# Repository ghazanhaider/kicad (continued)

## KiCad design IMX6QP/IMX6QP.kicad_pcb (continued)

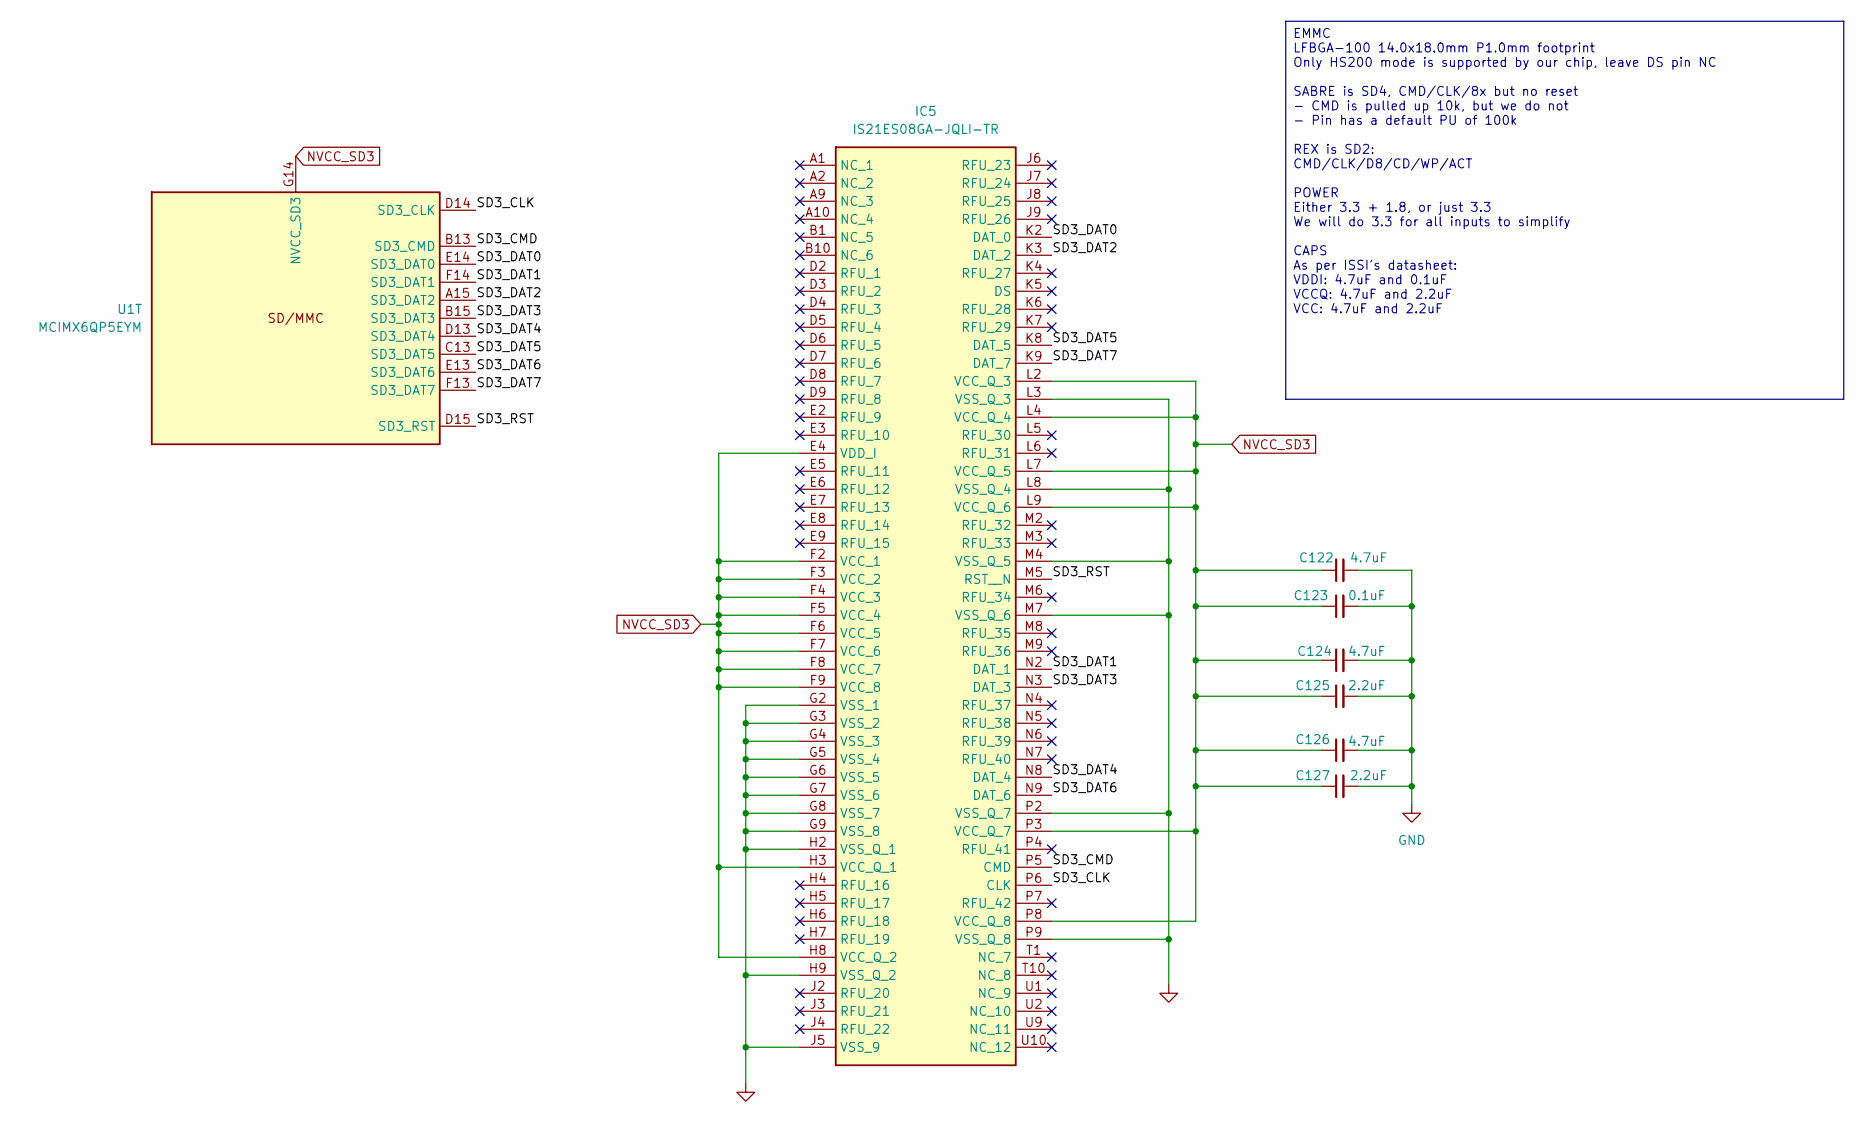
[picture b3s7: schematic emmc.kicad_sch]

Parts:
C122, C124, C126: 4.7uF; C_0603_1608Metric
C123: 0.1uF; C_0402_1005Metric
C125, C127: 2.2uF; C_0603_1608Metric
IC5: IS21ES08GA-JQLI-TR; BGA100C100P10X17_1400X1800X140; Mouser Part Number 870-IS21ES08GAJQLIT
U1: MCIMX6QP5EYM; BGA-624_21x21mm_Layout25x25_P0.8mm

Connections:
3V3_SW2: C122.1, C123.1, C124.1, C125.1, C126.1, C127.1, IC5.E4 (VDD_I), IC5.F2 (VCC_1), IC5.F3 (VCC_2), IC5.F4 (VCC_3), IC5.F5 (VCC_4), IC5.F6 (VCC_5), IC5.F7 (VCC_6), IC5.F8 (VCC_7), IC5.F9 (VCC_8), IC5.H3 (VCC_Q_1), IC5.H8 (VCC_Q_2), IC5.L2 (VCC_Q_3), IC5.L4 (VCC_Q_4), IC5.L7 (VCC_Q_5), IC5.L9 (VCC_Q_6), IC5.P3 (VCC_Q_7), IC5.P8 (VCC_Q_8), U1.G14 (NVCC_SD3); also elsewhere on the board
/eMMC/SD3_CLK: IC5.P6 (CLK), U1.D14 (SD3_CLK)
/eMMC/SD3_CMD: IC5.P5 (CMD), U1.B13 (SD3_CMD)
/eMMC/SD3_DAT0: IC5.K2 (DAT_0), U1.E14 (SD3_DAT0)
/eMMC/SD3_DAT1: IC5.N2 (DAT_1), U1.F14 (SD3_DAT1)
/eMMC/SD3_DAT2: IC5.K3 (DAT_2), U1.A15 (SD3_DAT2)
/eMMC/SD3_DAT3: IC5.N3 (DAT_3), U1.B15 (SD3_DAT3)
/eMMC/SD3_DAT4: IC5.N8 (DAT_4), U1.D13 (SD3_DAT4)
/eMMC/SD3_DAT5: IC5.K8 (DAT_5), U1.C13 (SD3_DAT5)
/eMMC/SD3_DAT6: IC5.N9 (DAT_6), U1.E13 (SD3_DAT6)
/eMMC/SD3_DAT7: IC5.K9 (DAT_7), U1.F13 (SD3_DAT7)
/eMMC/SD3_RST: IC5.M5 (RST__N), U1.D15 (SD3_RST)
GND: C122.2, C123.2, C124.2, C125.2, C126.2, C127.2, IC5.G2 (VSS_1), IC5.G3 (VSS_2), IC5.G4 (VSS_3), IC5.G5 (VSS_4), IC5.G6 (VSS_5), IC5.G7 (VSS_6), IC5.G8 (VSS_7), IC5.G9 (VSS_8), IC5.H2 (VSS_Q_1), IC5.H9 (VSS_Q_2), IC5.J5 (VSS_9), IC5.L3 (VSS_Q_3), IC5.L8 (VSS_Q_4), IC5.M4 (VSS_Q_5), IC5.M7 (VSS_Q_6), IC5.P2 (VSS_Q_7), IC5.P9 (VSS_Q_8); also elsewhere on the board

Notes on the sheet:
EMMC LFBGA-100 14.0x18.0mm P1.0mm footprint Only HS200 mode is supported by our chip, leave DS pin NC SABRE is SD4, CMD/CLK/8x but no reset - CMD is pulled up 10k, but we do not - Pin has a default PU of 100k REX is SD2: CMD/CLK/D8/CD/WP/ACT POWER Either 3.3 + 1.8, or just 3.3 We will do 3.3 for al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

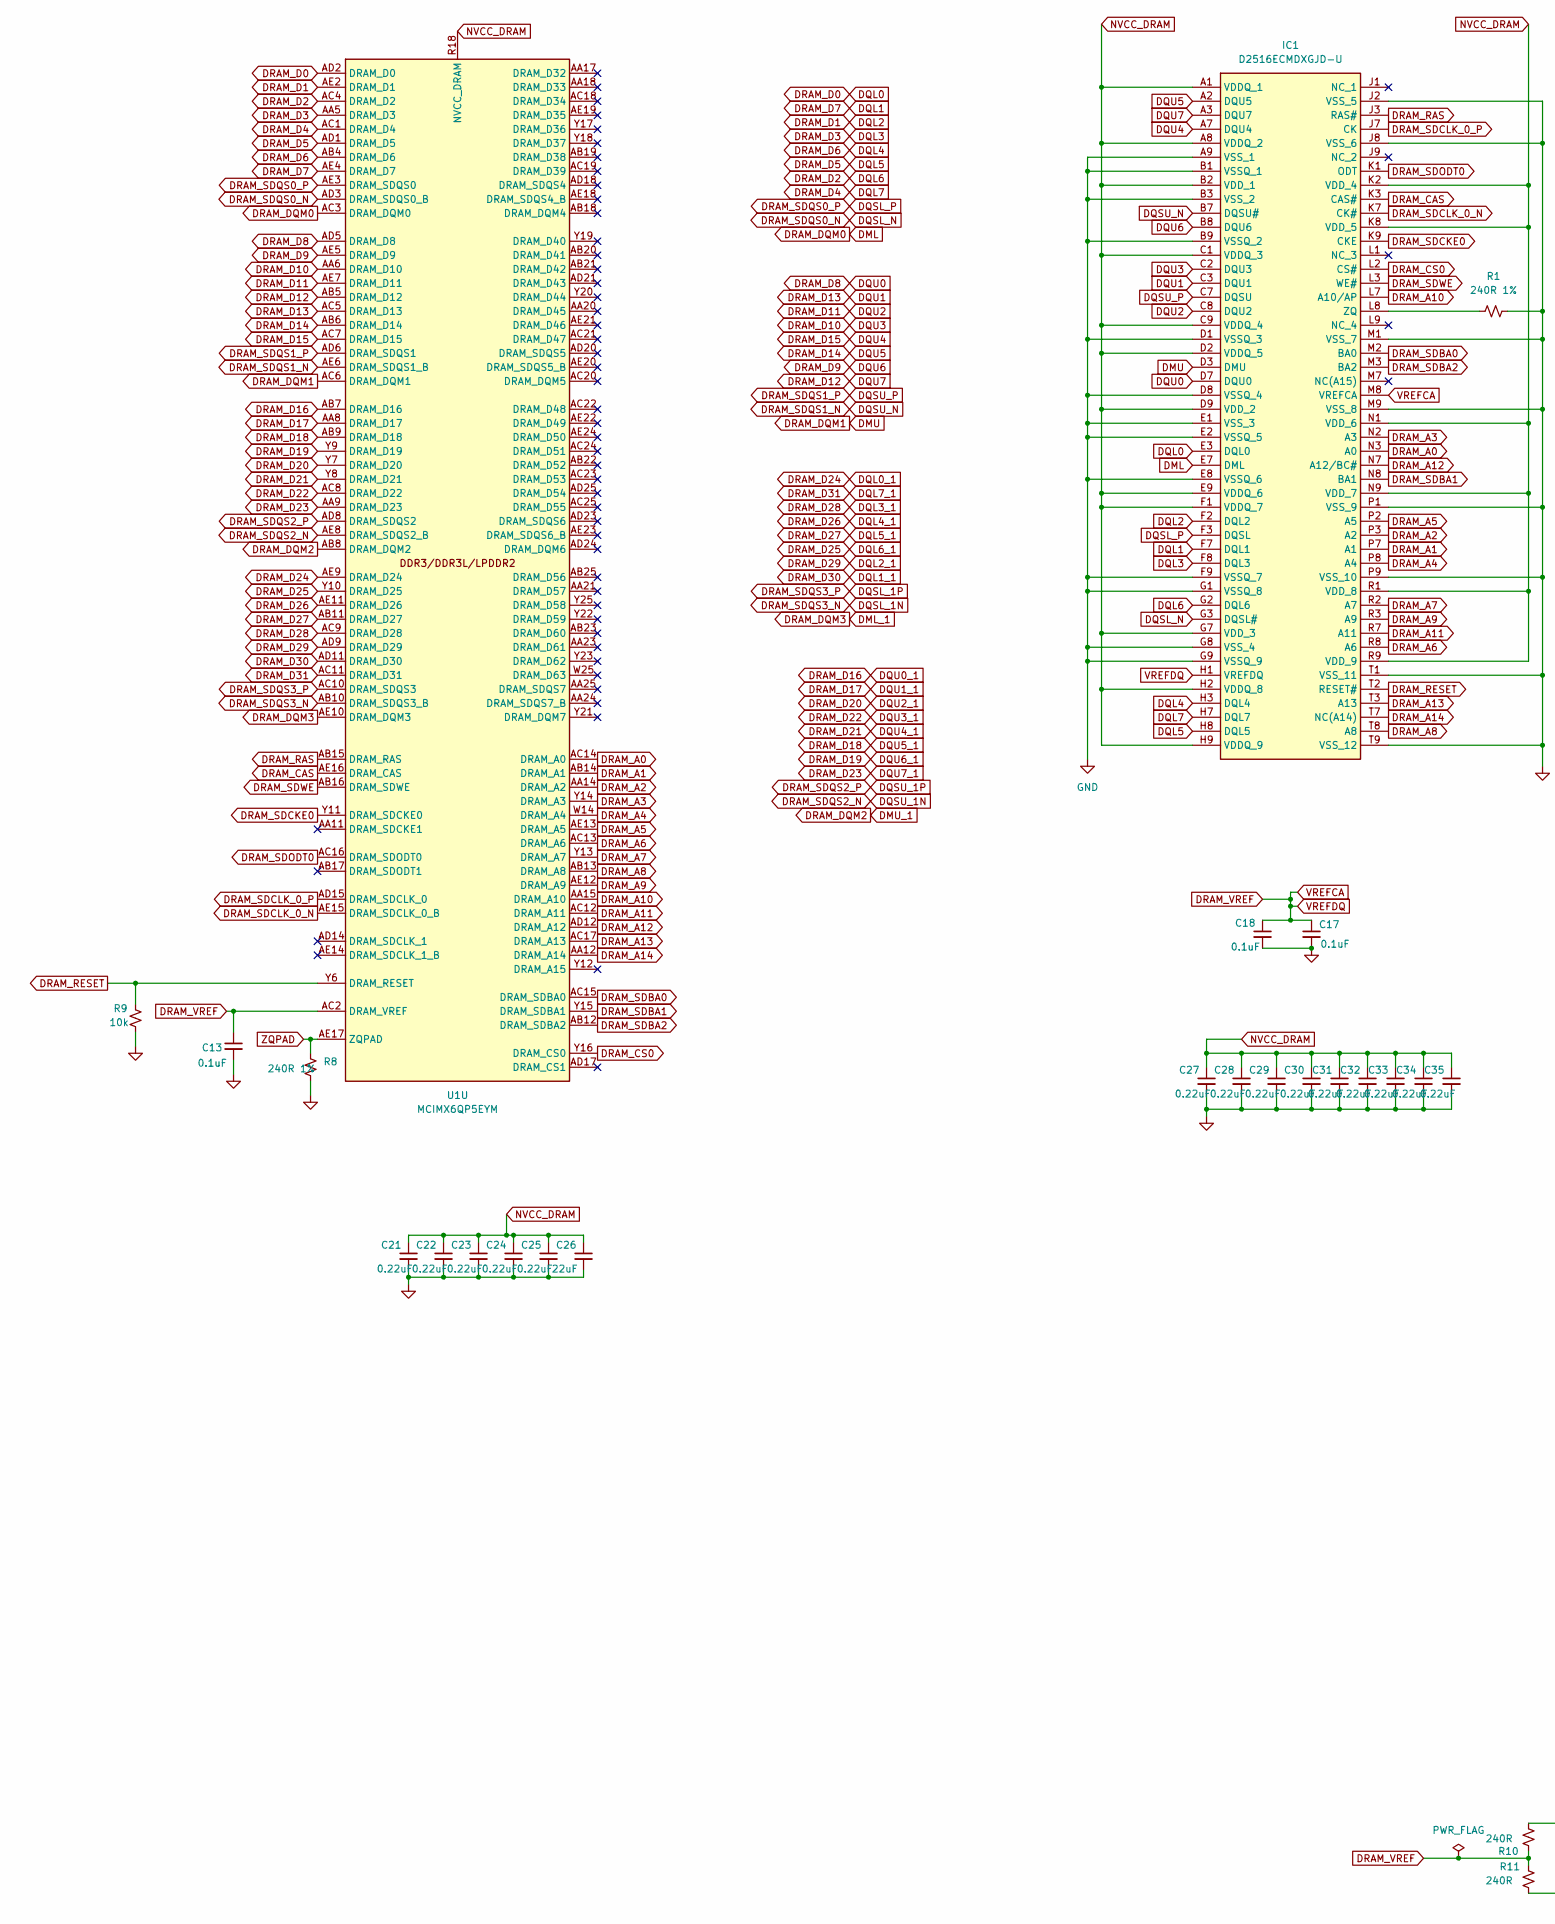
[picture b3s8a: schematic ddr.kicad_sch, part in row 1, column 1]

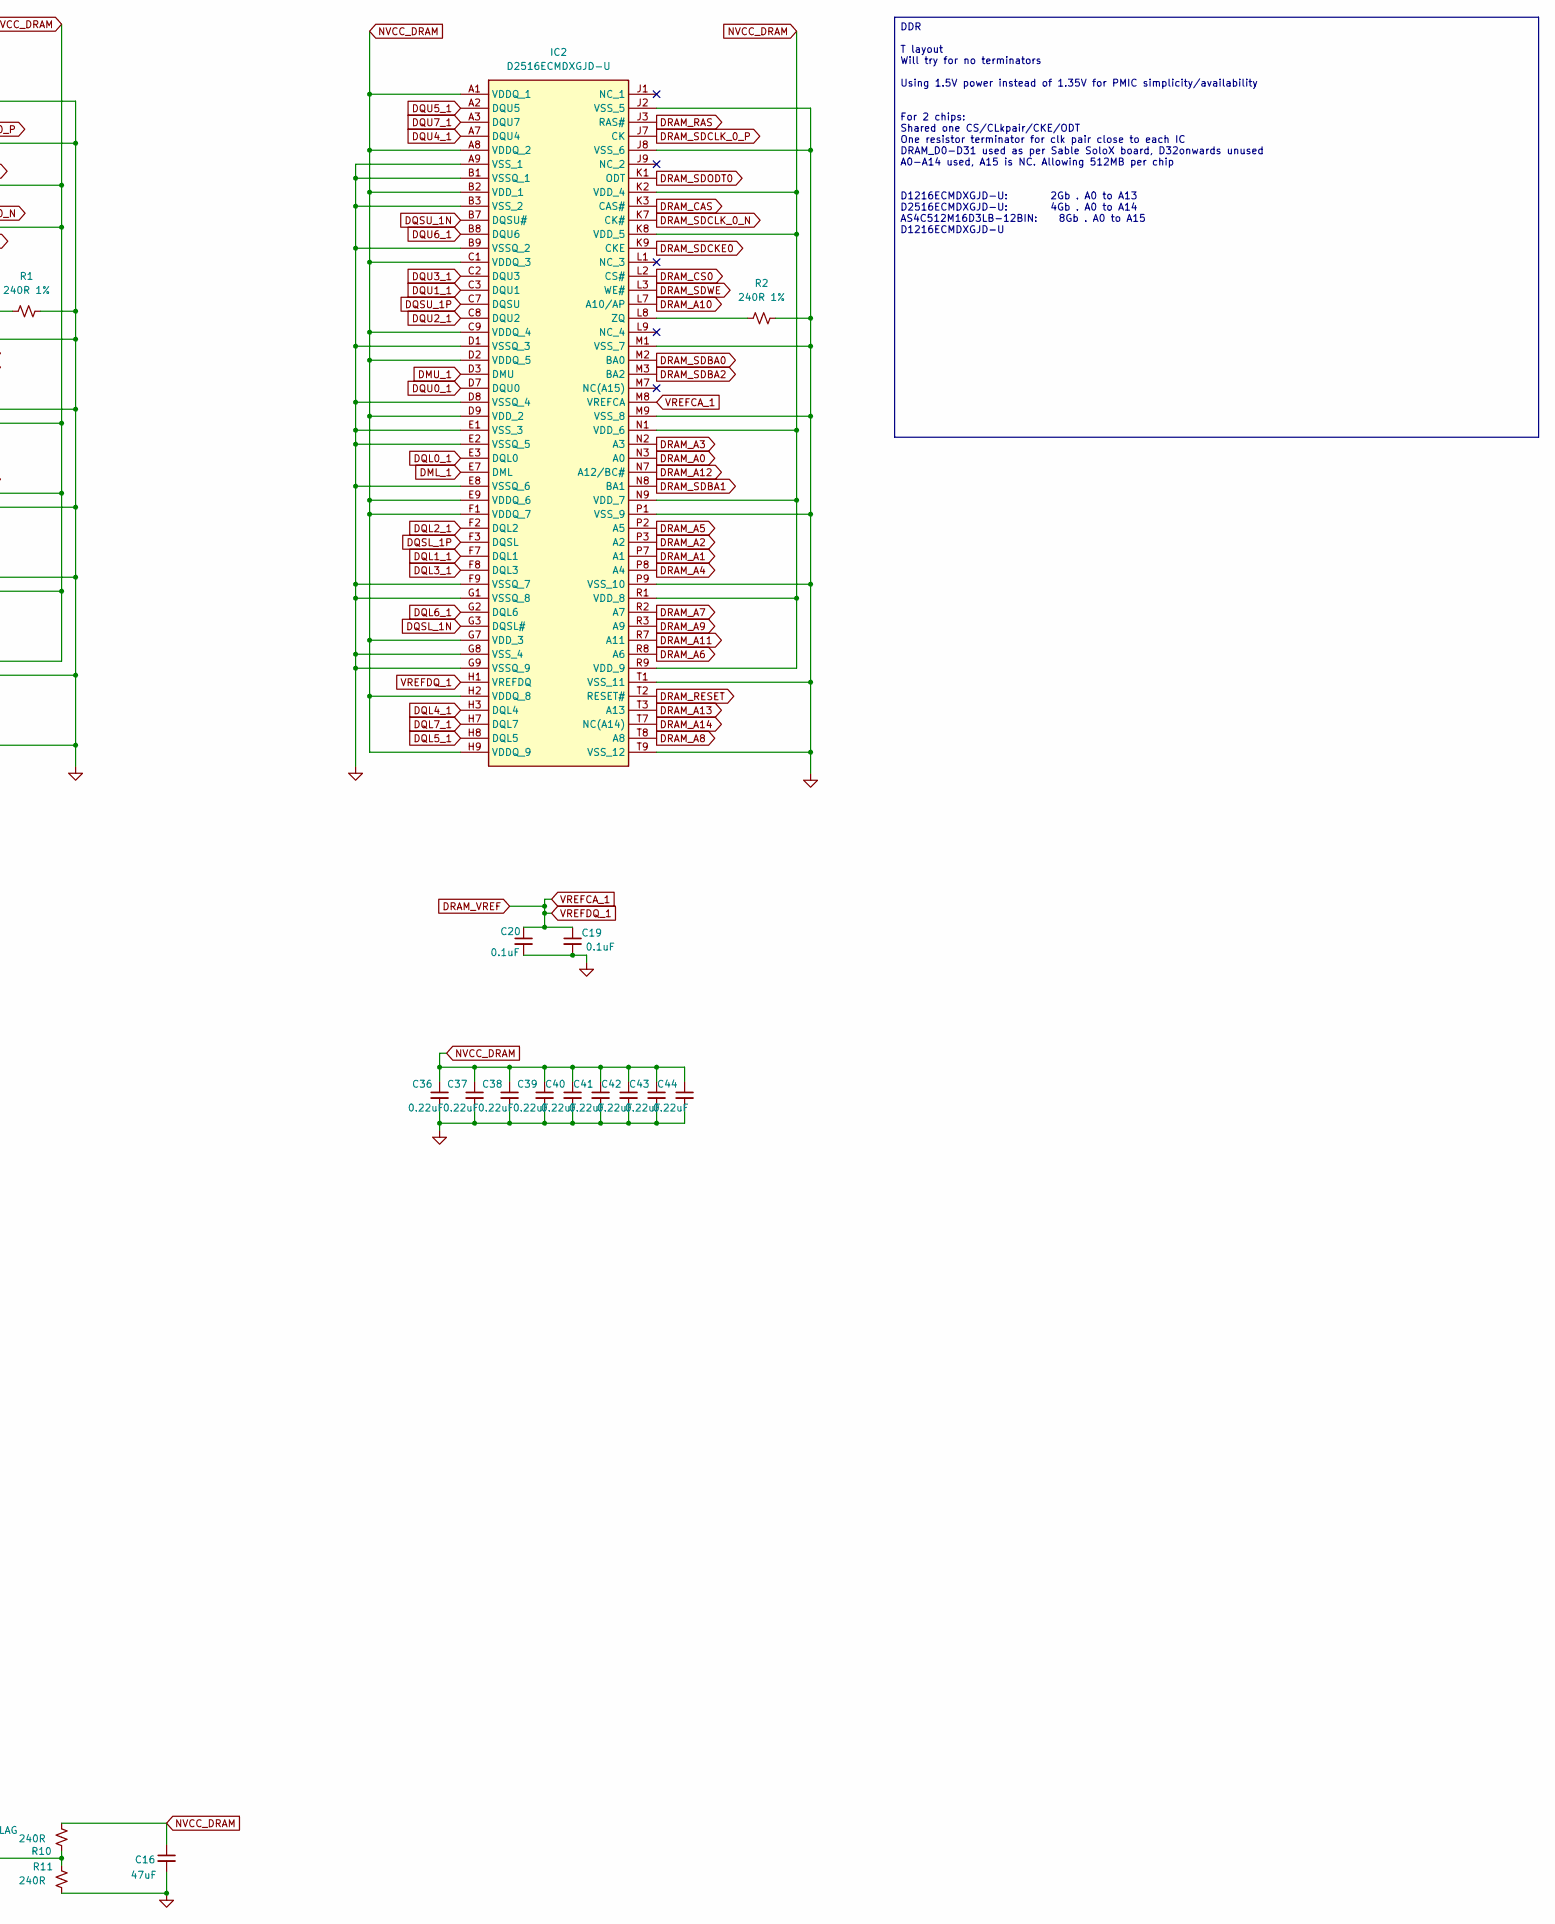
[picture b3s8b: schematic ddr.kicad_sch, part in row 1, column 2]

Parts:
C13, C17, C18, C19, C20: 0.1uF; C_0402_1005Metric
C16: 47uF; C_0402_1005Metric
C21, C22, C23, C24, C25, C27, C28, C29, C30, C31, C32, C33, C34, C35, C36, C37, C38, C39, C40, C41, C42, C43, C44: 0.22uF; C_0201_0603Metric
C26: 22uF; C_0402_1005Metric
IC1, IC2: D2516ECMDXGJD-U; BGA-96_9.0x13.0mm_Layout2x3x16_P0.8mm; Mouser Part Number D1216ECMDXGJD-U
R1, R2, R8: 240R 1%; R_0402_1005Metric
R9: 10k; R_0603_1608Metric
R10, R11: 240R; R_0402_1005Metric
U1: MCIMX6QP5EYM; BGA-624_21x21mm_Layout25x25_P0.8mm

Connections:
1V5_SW3: C16.1, C21.1, C22.1, C23.1, C24.1, C25.1, C26.1, C27.1, C28.1, C29.1, C30.1, C31.1, C32.1, C33.1, C34.1, C35.1, C36.1, C37.1, C38.1, C39.1, C40.1, C41.1, C42.1, C43.1, C44.1, IC1.A1 (VDDQ_1), IC1.A8 (VDDQ_2), IC1.B2 (VDD_1), IC1.C1 (VDDQ_3), IC1.C9 (VDDQ_4), IC1.D2 (VDDQ_5), IC1.D9 (VDD_2), IC1.E9 (VDDQ_6), IC1.F1 (VDDQ_7), IC1.G7 (VDD_3), IC1.H2 (VDDQ_8), IC1.H9 (VDDQ_9), IC1.K2 (VDD_4), IC1.K8 (VDD_5), IC1.N1 (VDD_6), IC1.N9 (VDD_7), IC1.R1 (VDD_8), IC1.R9 (VDD_9), IC2.A1 (VDDQ_1), IC2.A8 (VDDQ_2), IC2.B2 (VDD_1), IC2.C1 (VDDQ_3), IC2.C9 (VDDQ_4), IC2.D2 (VDDQ_5), IC2.D9 (VDD_2), IC2.E9 (VDDQ_6), IC2.F1 (VDDQ_7), IC2.G7 (VDD_3), IC2.H2 (VDDQ_8), IC2.H9 (VDDQ_9), IC2.K2 (VDD_4), IC2.K8 (VDD_5), IC2.N1 (VDD_6), IC2.N9 (VDD_7), IC2.R1 (VDD_8), IC2.R9 (VDD_9), R10.1, U1.R18 (NVCC_DRAM), U1.T18 (NVCC_DRAM), U1.U18 (NVCC_DRAM), U1.V9 (NVCC_DRAM), U1.V10 (NVCC_DRAM), U1.V11 (NVCC_DRAM), U1.V12 (NVCC_DRAM), U1.V13 (NVCC_DRAM), U1.V14 (NVCC_DRAM), U1.V15 (NVCC_DRAM), U1.V16 (NVCC_DRAM), U1.V17 (NVCC_DRAM), U1.V18 (NVCC_DRAM); also elsewhere on the board
DML: IC1.E7 (DML), U1.AC3 (DRAM_DQM0)
DML_1: IC2.E7 (DML), U1.AE10 (DRAM_DQM3)
DMU: IC1.D3 (DMU), U1.AC6 (DRAM_DQM1)
DMU_1: IC2.D3 (DMU), U1.AB8 (DRAM_DQM2)
DQL0: IC1.E3 (DQL0), U1.AD2 (DRAM_D0)
DQL0_1: IC2.E3 (DQL0), U1.AE9 (DRAM_D24)
DQL1: IC1.F7 (DQL1), U1.AE4 (DRAM_D7)
DQL1_1: IC2.F7 (DQL1), U1.AD11 (DRAM_D30)
DQL2: IC1.F2 (DQL2), U1.AE2 (DRAM_D1)
DQL2_1: IC2.F2 (DQL2), U1.AD9 (DRAM_D29)
DQL3: IC1.F8 (DQL3), U1.AA5 (DRAM_D3)
DQL3_1: IC2.F8 (DQL3), U1.AC9 (DRAM_D28)
DQL4: IC1.H3 (DQL4), U1.AB4 (DRAM_D6)
DQL4_1: IC2.H3 (DQL4), U1.AE11 (DRAM_D26)
DQL5: IC1.H8 (DQL5), U1.AD1 (DRAM_D5)
DQL5_1: IC2.H8 (DQL5), U1.AB11 (DRAM_D27)
DQL6: IC1.G2 (DQL6), U1.AC4 (DRAM_D2)
DQL6_1: IC2.G2 (DQL6), U1.Y10 (DRAM_D25)
DQL7: IC1.H7 (DQL7), U1.AC1 (DRAM_D4)
DQL7_1: IC2.H7 (DQL7), U1.AC11 (DRAM_D31)
DQSL_1N: IC2.G3 (DQSL#), U1.AB10 (DRAM_SDQS3_B)
DQSL_1P: IC2.F3 (DQSL), U1.AC10 (DRAM_SDQS3)
DQSL_N: IC1.G3 (DQSL#), U1.AD3 (DRAM_SDQS0_B)
DQSL_P: IC1.F3 (DQSL), U1.AE3 (DRAM_SDQS0)
DQSU_1N: IC2.B7 (DQSU#), U1.AE8 (DRAM_SDQS2_B)
DQSU_1P: IC2.C7 (DQSU), U1.AD8 (DRAM_SDQS2)
DQSU_N: IC1.B7 (DQSU#), U1.AE6 (DRAM_SDQS1_B)
DQSU_P: IC1.C7 (DQSU), U1.AD6 (DRAM_SDQS1)
DQU0: IC1.D7 (DQU0), U1.AD5 (DRAM_D8)
DQU0_1: IC2.D7 (DQU0), U1.AB7 (DRAM_D16)
DQU1: IC1.C3 (DQU1), U1.AC5 (DRAM_D13)
DQU1_1: IC2.C3 (DQU1), U1.AA8 (DRAM_D17)
DQU2: IC1.C8 (DQU2), U1.AE7 (DRAM_D11)
DQU2_1: IC2.C8 (DQU2), U1.Y7 (DRAM_D20)
DQU3: IC1.C2 (DQU3), U1.AA6 (DRAM_D10)
DQU3_1: IC2.C2 (DQU3), U1.AC8 (DRAM_D22)
DQU4: IC1.A7 (DQU4), U1.AC7 (DRAM_D15)
DQU4_1: IC2.A7 (DQU4), U1.Y8 (DRAM_D21)
DQU5: IC1.A2 (DQU5), U1.AB6 (DRAM_D14)
DQU5_1: IC2.A2 (DQU5), U1.AB9 (DRAM_D18)
DQU6: IC1.B8 (DQU6), U1.AE5 (DRAM_D9)
DQU6_1: IC2.B8 (DQU6), U1.Y9 (DRAM_D19)
DQU7: IC1.A3 (DQU7), U1.AB5 (DRAM_D12)
DQU7_1: IC2.A3 (DQU7), U1.AA9 (DRAM_D23)
DRAM_A0: IC1.N3 (A0), IC2.N3 (A0), U1.AC14 (DRAM_A0)
DRAM_A1: IC1.P7 (A1), IC2.P7 (A1), U1.AB14 (DRAM_A1)
DRAM_A2: IC1.P3 (A2), IC2.P3 (A2), U1.AA14 (DRAM_A2)
DRAM_A3: IC1.N2 (A3), IC2.N2 (A3), U1.Y14 (DRAM_A3)
DRAM_A4: IC1.P8 (A4), IC2.P8 (A4), U1.W14 (DRAM_A4)
DRAM_A5: IC1.P2 (A5), IC2.P2 (A5), U1.AE13 (DRAM_A5)
DRAM_A6: IC1.R8 (A6), IC2.R8 (A6), U1.AC13 (DRAM_A6)
DRAM_A7: IC1.R2 (A7), IC2.R2 (A7), U1.Y13 (DRAM_A7)
DRAM_A8: IC1.T8 (A8), IC2.T8 (A8), U1.AB13 (DRAM_A8)
DRAM_A9: IC1.R3 (A9), IC2.R3 (A9), U1.AE12 (DRAM_A9)
DRAM_A10: IC1.L7 (A10/AP), IC2.L7 (A10/AP), U1.AA15 (DRAM_A10)
DRAM_A11: IC1.R7 (A11), IC2.R7 (A11), U1.AC12 (DRAM_A11)
DRAM_A12: IC1.N7 (A12/BC#), IC2.N7 (A12/BC#), U1.AD12 (DRAM_A12)
DRAM_A13: IC1.T3 (A13), IC2.T3 (A13), U1.AC17 (DRAM_A13)
DRAM_A14: IC1.T7 (NC(A14)), IC2.T7 (NC(A14)), U1.AA12 (DRAM_A14)
DRAM_CAS: IC1.K3 (CAS#), IC2.K3 (CAS#), U1.AE16 (DRAM_CAS)
DRAM_CS0: IC1.L2 (CS#), IC2.L2 (CS#), U1.Y16 (DRAM_CS0)
DRAM_RAS: IC1.J3 (RAS#), IC2.J3 (RAS#), U1.AB15 (DRAM_RAS)
DRAM_RESET: IC1.T2 (RESET#), IC2.T2 (RESET#), R9.1, U1.Y6 (DRAM_RESET)
DRAM_SDBA0: IC1.M2 (BA0), IC2.M2 (BA0), U1.AC15 (DRAM_SDBA0)
DRAM_SDBA1: IC1.N8 (BA1), IC2.N8 (BA1), U1.Y15 (DRAM_SDBA1)
DRAM_SDBA2: IC1.M3 (BA2), IC2.M3 (BA2), U1.AB12 (DRAM_SDBA2)
DRAM_SDCKE0: IC1.K9 (CKE), IC2.K9 (CKE), U1.Y11 (DRAM_SDCKE0)
DRAM_SDCLK_0_N: IC1.K7 (CK#), IC2.K7 (CK#), U1.AE15 (DRAM_SDCLK_0_B)
DRAM_SDCLK_0_P: IC1.J7 (CK), IC2.J7 (CK), U1.AD15 (DRAM_SDCLK_0)
DRAM_SDODT0: IC1.K1 (ODT), IC2.K1 (ODT), U1.AC16 (DRAM_SDODT0)
DRAM_SDWE: IC1.L3 (WE#), IC2.L3 (WE#), U1.AB16 (DRAM_SDWE)
DRAM_VREF: C13.1, C17.1, C18.1, C19.1, C20.1, IC1.H1 (VREFDQ), IC1.M8 (VREFCA), IC2.H1 (VREFDQ), IC2.M8 (VREFCA), R10.2, R11.1, U1.AC2 (DRAM_VREF)
GND: C13.2, C16.2, C17.2, C18.2, C19.2, C20.2, C21.2, C22.2, C23.2, C24.2, C25.2, C26.2, C27.2, C28.2, C29.2, C30.2, C31.2, C32.2, C33.2, C34.2, C35.2, C36.2, C37.2, C38.2, C39.2, C40.2, C41.2, C42.2, C43.2, C44.2, IC1.A9 (VSS_1), IC1.B1 (VSSQ_1), IC1.B3 (VSS_2), IC1.B9 (VSSQ_2), IC1.D1 (VSSQ_3), IC1.D8 (VSSQ_4), IC1.E1 (VSS_3), IC1.E2 (VSSQ_5), IC1.E8 (VSSQ_6), IC1.F9 (VSSQ_7), IC1.G1 (VSSQ_8), IC1.G8 (VSS_4), IC1.G9 (VSSQ_9), IC1.J2 (VSS_5), IC1.J8 (VSS_6), IC1.M1 (VSS_7), IC1.M9 (VSS_8), IC1.P1 (VSS_9), IC1.P9 (VSS_10), IC1.T1 (VSS_11), IC1.T9 (VSS_12), IC2.A9 (VSS_1), IC2.B1 (VSSQ_1), IC2.B3 (VSS_2), IC2.B9 (VSSQ_2), IC2.D1 (VSSQ_3), IC2.D8 (VSSQ_4), IC2.E1 (VSS_3), IC2.E2 (VSSQ_5), IC2.E8 (VSSQ_6), IC2.F9 (VSSQ_7), IC2.G1 (VSSQ_8), IC2.G8 (VSS_4), IC2.G9 (VSSQ_9), IC2.J2 (VSS_5), IC2.J8 (VSS_6), IC2.M1 (VSS_7), IC2.M9 (VSS_8), IC2.P1 (VSS_9), IC2.P9 (VSS_10), IC2.T1 (VSS_11), IC2.T9 (VSS_12), R1.2, R2.2, R8.2, R9.2, R11.2; also elsewhere on the board
unnamed: IC1.L8 (ZQ), R1.1
unnamed: IC2.L8 (ZQ), R2.1
ZQPAD: R8.1, U1.AE17 (ZQPAD)

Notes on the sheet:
DDR T layout Will try for no terminators Using 1.5V power instead of 1.35V for PMIC simplicity/availability For 2 chips: Shared one CS/CLkpair/CKE/ODT One resistor terminator for clk pair close to each IC DRAM_D0-D31 used as per Sable SoloX board, D32onwards unused A0-A14 used, A15 is NC. Allowing 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

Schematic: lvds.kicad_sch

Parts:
C130: 10uF; C_0603_1608Metric
C141: 0.22uF; C_0402_1005Metric
J15: LVDS; PinHeader_2x15_P2.00mm_Vertical
U1: MCIMX6QP5EYM; BGA-624_21x21mm_Layout25x25_P0.8mm

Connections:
3V3_SW2: C130.2, J15.1, J15.2, J15.3; also elsewhere on the board
GND: C130.1, C141.1, J15.4, J15.5, J15.6, J15.13, J15.14, J15.25, J15.26; also elsewhere on the board
HDMI_VPH: C141.2, U1.V7 (NVCC_LVDS2P5); also elsewhere on the board
LVDS0_CLK_N: J15.15, U1.V4 (LVDS0_CLK_N)
LVDS0_CLK_P: J15.16, U1.V3 (LVDS0_CLK_P)
LVDS0_TX0_N: J15.7, U1.U2 (LVDS0_TX0_N)
LVDS0_TX0_P: J15.8, U1.U1 (LVDS0_TX0_P)
LVDS0_TX1_N: J15.9, U1.U4 (LVDS0_TX1_N)
LVDS0_TX1_P: J15.10, U1.U3 (LVDS0_TX1_P)
LVDS0_TX2_N: J15.11, U1.V2 (LVDS0_TX2_N)
LVDS0_TX2_P: J15.12, U1.V1 (LVDS0_TX2_P)
LVDS0_TX3_N: J15.17, U1.W2 (LVDS0_TX3_N)
LVDS0_TX3_P: J15.18, U1.W1 (LVDS0_TX3_P)

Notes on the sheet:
LVDS Using 2x15 (2mm pitch) cable connector found on T-60S We can try the cables that come with T-60S I2C/EDID - LVDS doesnt have its own pins, others use I2C2 pins Example Thinkpad LCDs: Thinkpad T40: IAXG15s (30 pins 1ch 6bit LVDS, VCC is 3.3V) Thinkpad T400: LTN141AT09 (uses connector: FI-XB30SR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

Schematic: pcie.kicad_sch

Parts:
C61, C62, C120, C121: 0.1uF; C_0402_1005Metric
C63: 10uF; C_0603_1608Metric
J8: Bus_PCI_Express_x1; 1001878311200TLF
J17: PCIE_12V; PinHeader_1x02_P2.54mm_Vertical
R27: 200R 1%; R_0603_1608Metric
R35: 10k 1%; R_0603_1608Metric
U1: MCIMX6QP5EYM; BGA-624_21x21mm_Layout25x25_P0.8mm

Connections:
3V3_SW2: J8.A9 (+3.3V), J8.A10 (+3.3V), J8.B8 (+3.3V), J8.B10 (3.3Vaux), R35.1; also elsewhere on the board
/PCIe/PCIE_REXT: R27.1, U1.A2 (PCIE_REXT)
CLK1_N: J8.A14 (REFCLK-); also elsewhere on the board
CLK1_P: J8.A13 (REFCLK+); also elsewhere on the board
GND: C63.2, J8.1 (GND), J8.2 (GND), J8.A1 (~PRSNT1), J8.A4 (GND), J8.A12 (GND), J8.A15 (GND), J8.A18 (GND), J8.B4 (GND), J8.B7 (GND), J8.B13 (GND), J8.B16 (GND), J8.B18 (GND), J17.1, R27.2; also elsewhere on the board
HDMI_VP: U1.G8 (PCIE_VPTX), U1.H7 (PCIE_VP); also elsewhere on the board
HDMI_VPH: U1.G7 (PCIE_VPH); also elsewhere on the board
MLB_SN: J8.A11 (~PERST); also elsewhere on the board
unnamed: J8.B17 (~PRSNT2), R35.2
unnamed: C63.1, J8.A2 (+12V), J8.A3 (+12V), J8.B1 (+12V), J8.B2 (+12V), J8.B3 (+12V), J17.2
unnamed: C61.1, U1.B1 (PCIE_RXM)
unnamed: C62.1, U1.B2 (PCIE_RXP)
unnamed: C120.1, U1.A3 (PCIE_TXM)
unnamed: C121.1, U1.B3 (PCIE_TXP)
PCIE_RXM: C61.2, J8.A17 (PERn0)
PCIE_RXP: C62.2, J8.A16 (PERp0)
PCIE_TXM: C120.2, J8.B15 (PETn0)
PCIE_TXP: C121.2, J8.B14 (PETp0)

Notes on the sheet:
PCIe 2.0 5Gbps and 1.1 2.5Gbps Pinouts we'll use: TX pair RX pair CLK pair 3.3V and 3.3Aux PERST (wake up/rest card): uses reset-gpios in dts Wont use: JTAG (NC) SMbus (NC) WAKE (devicetree wake-gpios) (opendrain, NC) CLKREQ (devicetree supports-clkreq) (?? pull where ??) ? PRSNT pair 3.3V: Powered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

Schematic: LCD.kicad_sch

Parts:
C11, C12, C53: 1uF; C_0402_1005Metric
C60: 0.1uF; C_0402_1005Metric
D1: 1N5819HW-7-F; D_SOD-123
J3: Conn_01x40; Hirose_FH12-40S-0.5SH_1x40-1MP_P0.50mm_Horizontal
JP4: BL_PWR_SRC; SolderJumper-3_P1.3mm_Open_RoundedPad1.0x1.5mm_NumberLabels
L1: 15uH NLCV32T-150K-EF; L_1210_3225Metric
R7: 4.7k; R_0603_1608Metric
R32: 56k; R_0603_1608Metric
TP1: Backlight; TestPoint_Loop_D1.80mm_Drill1.0mm_Beaded
U1: MCIMX6QP5EYM; BGA-624_21x21mm_Layout25x25_P0.8mm
U6: AP3012; SOT-23-5

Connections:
3V3_SW2: C53.2, C60.2, J3.4, U1.P19 (NVCC_LCD); also elsewhere on the board
5V0_USB: JP4.1 (A); also elsewhere on the board
BLUE0: J3.21, U1.P24 (DISP0_DAT0)
BLUE1: J3.22, U1.P22 (DISP0_DAT1)
BLUE2: J3.23, U1.P23 (DISP0_DAT2)
BLUE3: J3.24, U1.P21 (DISP0_DAT3)
BLUE4: J3.25, U1.P20 (DISP0_DAT4)
BLUE5: J3.26, U1.R25 (DISP0_DAT5)
BLUE6: J3.27, U1.R23 (DISP0_DAT6)
BLUE7: J3.28, U1.R24 (DISP0_DAT7)
DATA_EN: J3.34, U1.N21 (DI0_PIN15)
DI0_DISP_CLK: J3.30, U1.N19 (DI0_DISP_CLK)
EIM_WAIT: U6.4 (~SHDN); also elsewhere on the board
GND: C11.1, C12.2, C53.1, C60.1, J3.1, J3.3, J3.29, J3.36, J3.MP, R7.2, U6.2 (GND); also elsewhere on the board
GREEN0: J3.13, U1.R22 (DISP0_DAT8)
GREEN1: J3.14, U1.T25 (DISP0_DAT9)
GREEN2: J3.15, U1.R21 (DISP0_DAT10)
GREEN3: J3.16, U1.T23 (DISP0_DAT11)
GREEN4: J3.17, U1.T24 (DISP0_DAT12)
GREEN5: J3.18, U1.R20 (DISP0_DAT13)
GREEN6: J3.19, U1.U25 (DISP0_DAT14)
GREEN7: J3.20, U1.T22 (DISP0_DAT15)
HSYNC: J3.32, U1.N25 (DI0_PIN2)
unnamed: D1.2 (A), L1.2, U6.1 (SW)
unnamed: C12.1, D1.1 (K), J3.2, R32.1, TP1.1
unnamed: C11.2, JP4.2 (C), L1.1, U6.5 (IN)
unnamed: R7.1, R32.2, U6.3 (FB)
PMIC_VIN: JP4.3 (B); also elsewhere on the board
RED0: J3.5, U1.T21 (DISP0_DAT16)
RED1: J3.6, U1.U24 (DISP0_DAT17)
RED2: J3.7, U1.V25 (DISP0_DAT18)
RED3: J3.8, U1.U23 (DISP0_DAT19)
RED4: J3.9, U1.U22 (DISP0_DAT20)
RED5: J3.10, U1.T20 (DISP0_DAT21)
RED6: J3.11, U1.V24 (DISP0_DAT22)
RED7: J3.12, U1.W24 (DISP0_DAT23)
VSYNC: J3.33, U1.N20 (DI0_PIN3)

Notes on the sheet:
LCD interface Designed for max 800x480 similar to this: https://www.buydisplay.com/ips-5-tft-lcd-display-module-wvga-800x480-high-resolution-for-mp4-gps RESISTOR DIVIDER AND VOUT Vout = 1.25 * (1 + (R32 / R7)) For 18V: R32 = 68.34k (appx) R7 = 5.1k 56k/5.1k = 15V 56k/4.7k = 16.14V <====== 100k/5.62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

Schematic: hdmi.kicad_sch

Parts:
C131, C138, C139: 0.1uF; C_0402_1005Metric
C136, C137: 0.22uF; C_0402_1005Metric
C140: 4.7uF; C_0603_1608Metric
IC6: TPD12S016PWR; SOP65P640X120-24N; Mouser Part Number 595-TPD12S016PWR
J7: HDMI_A_1.4; HDMI_A_Molex_208658-1001_Horizontal
JP7: LS_EN; SolderJumper-3_P1.3mm_Open_RoundedPad1.0x1.5mm_NumberLabels
R28: 1.6K 1%; R_0402_1005Metric
U1: MCIMX6QP5EYM; BGA-624_21x21mm_Layout25x25_P0.8mm

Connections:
3V3_SW2: C138.1, IC6.24 (VCCA), JP7.1 (A); also elsewhere on the board
5V0_USB: C139.2, C140.2, IC6.11 (VCC5V); also elsewhere on the board
/HDMI/HDMI_HPD: IC6.4 (HPD_A-), IC6.5 (LS_OE), U1.K1 (HDMI_HPD)
GND: C131.2, C136.1, C137.2, C138.2, C139.1, C140.1, IC6.6 (GND_1), IC6.14 (GND_2), IC6.19 (GND_3), J7.2 (D2S), J7.5 (D1S), J7.8 (D0S), J7.11 (CKS), J7.17 (GND), J7.SH, JP7.3 (B), R28.1, U1.K2 (HDMI_DDCCEC); also elsewhere on the board
HDMI_TX_CEC_LINE: IC6.1 (CEC_A); also elsewhere on the board
HDMI_TX_DDC_SCL: IC6.2 (SCL_A); also elsewhere on the board
HDMI_TX_DDC_SDA: IC6.3 (SDA_A); also elsewhere on the board
HDMI_VP: C136.2, U1.L7 (HDMI_VP); also elsewhere on the board
HDMI_VPH: C137.1, U1.M7 (HDMI_VPH); also elsewhere on the board
unnamed: C131.1, IC6.13 (5V_OUT), J7.18 (+5V)
unnamed: IC6.7 (CEC_B), J7.13 (CEC)
unnamed: IC6.16 (CLK+), J7.10 (CK+), U1.J6 (HDMI_CLKP)
unnamed: IC6.15 (CLK-), J7.12 (CK-), U1.J5 (HDMI_CLKM)
unnamed: IC6.12 (CT_HPD), JP7.2 (C)
unnamed: IC6.18 (D0+), J7.7 (D0+), U1.K6 (HDMI_D0P)
unnamed: IC6.17 (D0-), J7.9 (D0-), U1.K5 (HDMI_D0M)
unnamed: IC6.21 (D1+), J7.4 (D1+), U1.J4 (HDMI_D1P)
unnamed: IC6.20 (D1-), J7.6 (D1-), U1.J3 (HDMI_D1M)
unnamed: IC6.23 (D2+), J7.1 (D2+), U1.K4 (HDMI_D2P)
unnamed: IC6.22 (D2-), J7.3 (D2-), U1.K3 (HDMI_D2M)
unnamed: IC6.10 (HPD_B-), J7.19 (HPD/HEAC-)
unnamed: IC6.8 (SCL_B), J7.15 (SCL)
unnamed: IC6.9 (SDA_B), J7.16 (SDA)
unnamed: R28.2, U1.J1 (HDMI_REF)

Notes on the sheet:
GND reference for HDMI CEC
HDMI Not using stock I2Cs. The Soc already has HDMI_TX_DDC I2C NVCC_GPIO is the reference pin for the I2C and CEC pins so we should use it for VCCA as well. TPD12S016PWR: VCCA should be same source as HDMI controllers HPD/CEC and I2C Vc SABRE uses CM2020(allpins), we use TPD12S016PWR for protection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

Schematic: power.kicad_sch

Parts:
BT1: Supercap; RSCSK2243R3D02008U
C1, C2: 10pF; C_0402_1005Metric
C14, C15, C46, C48, C50, C52, C54, C57, C59, C65, C71, C72, C104: 0.1uF; C_0402_1005Metric
C45, C47, C49, C51, C55, C58: 4.7uF; C_0603_1608Metric
C64, C112, C114, C117: 2.2uF; C_0603_1608Metric
C66, C88, C89: 1uF; C_0402_1005Metric
C73, C81, C82, C83: 10uF; C_0402_1005Metric
C75, C76, C77, C78, C79, C80, C90, C91, C92, C93, C94, C95, C96, C97, C100, C101, C102, C103, C111, C118: 22uF; C_0603_1608Metric
C84, C87, C106, C107, C110: 0.22uF; C_0402_1005Metric
C85, C86: 22pF; C_0402_1005Metric
C105, C109, C119: 22uF; C_0805_2012Metric
C108: 560pF; C_0402_1005Metric
H1, H2, H3, H4, H5, H6, H7, H8: MountingHole_Pad; MountingHole_2.5mm_Pad_TopBottom
IC3: MMPF0100F0ANES; QFN50P800X800X90-57N-D; Manufacturer_Part_Number MMPF0100F0ANES; Mouser Part Number 841-MMPF0100F0ANES
J1: USB1 PWR; USB_C_Receptacle_GCT_USB4105-xx-A_16P_TopMnt_Horizontal
J2: USB2 HOST; USB_C_Receptacle_GCT_USB4105-xx-A_16P_TopMnt_Horizontal
J10: BOOT0; PinHeader_1x02_P2.54mm_Vertical
J11: BOOT1; PinHeader_1x02_P2.54mm_Vertical
J12: BYPASS_PWR; PinHeader_1x03_P2.54mm_Vertical
JP1: OTP_PROG; SolderJumper-2_P1.3mm_Open_RoundedPad1.0x1.5mm
JP2: USB_PWR; SolderJumper-2_P1.3mm_Bridged_RoundedPad1.0x1.5mm
JP3: DEF_PWR; SolderJumper-2_P1.3mm_Bridged_RoundedPad1.0x1.5mm
JP5: 1.0V; SolderJumper-2_P1.3mm_Open_RoundedPad1.0x1.5mm
JP6: 2.5V; SolderJumper-2_P1.3mm_Open_RoundedPad1.0x1.5mm
L2, L3, L5, L6: 1uH; L_1008_2520Metric
L7: 2uH; L_Wurth_WE-LQSH-4020
R6, R37: 4.7k; R_0603_1608Metric
R12: 2.2Mohm; R_0603_1608Metric
R13, R14, R15, R30: 100K; R_0402_1005Metric
R16, R17: 330k; R_0402_1005Metric
R18: 33k; R_0402_1005Metric
R19: 75k; R_0402_1005Metric
R20: 24k; R_0402_1005Metric
R21, R22: 5.1k; R_0402_1005Metric
R23, R24: 56k; R_0603_1608Metric
R38: 100m; R_0402_1005Metric
RT1: HSOP-8-1EP_3.9x4.9mm_P1.27mm_EP2.3x2.3mm
SW1: ONOFF; SW_SPST_EVPBF
SW2: RESET; SW_SPST_EVPBF
TP2: OTP 8.25V; TestPoint_Loop_D1.80mm_Drill1.0mm_Beaded
U1: MCIMX6QP5EYM; BGA-624_21x21mm_Layout25x25_P0.8mm
U2: ARM-JTAG-SWD; ARM-JTAG-10-SWD-IDC
Y1: 24MHz; Crystal_SMD_2016-4Pin_2.0x1.6mm
Y3: 32kHz; Crystal_SMD_3215-2Pin_3.2x1.5mm

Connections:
1V3_SW1AB: C90.1, C92.1, C93.1, C94.1, IC3.6 (SW1FB), L2.1, U1.H14 (VDD_ARM_IN), U1.J14 (VDD_ARM_IN), U1.K9 (VDD_ARM23_IN), U1.K14 (VDD_ARM_IN), U1.L9 (VDD_ARM23_IN), U1.L14 (VDD_ARM_IN), U1.M9 (VDD_ARM23_IN), U1.M14 (VDD_ARM_IN), U1.N9 (VDD_ARM23_IN), U1.N14 (VDD_ARM_IN), U1.P9 (VDD_ARM23_IN), U1.P14 (VDD_ARM_IN), U1.R9 (VDD_ARM23_IN), U1.R14 (VDD_ARM_IN), U1.T9 (VDD_ARM23_IN), U1.U9 (VDD_ARM23_IN)
1V3_SW1C: C75.1, C91.1, C95.1, IC3.13 (SW1CFB), L3.1, U1.H16 (VDD_SOC_IN), U1.J16 (VDD_SOC_IN), U1.K16 (VDD_SOC_IN), U1.L16 (VDD_SOC_IN), U1.M16 (VDD_SOC_IN), U1.N16 (VDD_SOC_IN), U1.P16 (VDD_SOC_IN), U1.R16 (VDD_SOC_IN), U1.T16 (VDD_SOC_IN), U1.U16 (VDD_SOC_IN)
1V5_SW3: C14.1, C100.1, C101.1, C102.2, C103.1, C114.1, IC3.30 (VINREFDDR), IC3.38 (SW3AFB), L6.2; also elsewhere on the board
3V3_SW2: C96.1, C97.1, IC3.25 (SW2FB), L5.1, U1.H9 (VDD_HIGH_IN), U1.J7 (NVCC_JTAG), U1.J9 (VDD_HIGH_IN), U2.1 (VREF); also elsewhere on the board
5V0_USB: C105.2, C106.2, C111.2, C112.2, C117.2, C118.2, J1.A4 (VBUS), J1.A9 (VBUS), J1.B4 (VBUS), J1.B9 (VBUS), J2.A4 (VBUS), J2.A9 (VBUS), J2.B4 (VBUS), J2.B9 (VBUS), R16.1, R23.2, R24.2, RT1.4 (VIN), U1.D10 (USB_H1_VBUS), U1.E9 (USB_OTG_VBUS); also elsewhere on the board
/Power/JTAG_TCK: U1.H5 (JTAG_TCK), U2.4 (SWCLK/TCK)
/Power/JTAG_TDI: U1.G5 (JTAG_TDI), U2.8 (NC/TDI)
/Power/JTAG_TDO: U1.G6 (JTAG_TDO), U2.6 (SWO/TDO)
/Power/JTAG_TMS: U1.C3 (JTAG_TMS), U2.2 (SWDIO/TMS)
/Power/JTAG_TRSTB: U1.C2 (JTAG_TRSTB), U2.10 (nRESET)
/Power/RTC_XTALI: C85.1, U1.D9 (RTC_XTALI), Y3.2
/Power/RTC_XTALO: C86.1, U1.C9 (RTC_XTALO), Y3.1
/Power/XTALI: C1.1, R12.1, U1.A7 (XTALI), Y1.1
/Power/XTALO: C2.1, U1.B7 (XTALO), Y1.3
BOOT_MODE0: J10.1, U1.C12 (BOOT_MODE0)
BOOT_MODE1: J11.1, U1.F12 (BOOT_MODE1)
CLK1_N: U1.C7 (CLK1_N); also elsewhere on the board
CLK1_P: U1.D7 (CLK1_P); also elsewhere on the board
CSI_D1M: IC3.1 (INTB), R13.2; also elsewhere on the board
CSI_D1P: IC3.2 (SDWNB), R14.2; also elsewhere on the board
DRAM_VREF_2: C66.1, IC3.31 (VREFDDR)
GETH_1V: JP5.2 (B); also elsewhere on the board
GETH_2V5: JP6.2 (B); also elsewhere on the board
GND: BT1.2 (-), C1.2, C2.2, C15.2, C45.1, C46.1, C47.1, C48.1, C49.1, C50.1, C51.1, C52.1, C54.1, C55.2, C57.2, C58.2, C59.2, C64.2, C65.1, C66.2, C71.2, C72.2, C73.2, C75.2, C76.2, C77.2, C78.2, C79.2, C80.2, C81.2, C82.2, C83.2, C84.2, C85.2, C86.2, C87.2, C88.2, C89.2, C90.2, C91.2, C92.2, C93.2, C94.2, C95.2, C96.2, C97.2, C100.2, C101.2, C102.1, C103.2, C104.2, C105.1, C106.1, C107.1, C108.1, C109.1, C110.1, C111.1, C112.1, C114.2, C117.1, C118.1, C119.1, H1.1, H2.1, H3.1, H4.1, H5.1, H6.1, H7.1, H8.1, IC3.5 (ICTEST), IC3.14 (SW1VSSSNS), IC3.15 (GNDREF1), IC3.32 (SW3VSSSNS), IC3.48 (GNDREF), IC3.57 (EP), J1.A1 (GND), J1.A12 (GND), J1.B1 (GND), J1.B12 (GND), J1.S1 (SHIELD), J2.A1 (GND), J2.A12 (GND), J2.B1 (GND), J2.B12 (GND), J2.S1 (SHIELD), J12.3, R12.2, R17.1, R20.1, R21.1, R22.1, RT1.9 (GND), SW1.2, SW2.1, U1.A4 (GND), U1.A8 (GND), U1.A13 (GND), U1.A25 (GND), U1.AA7 (GND), U1.AA10 (GND), U1.AA13 (GND), U1.AA16 (GND), U1.AA19 (GND), U1.AA22 (GND), U1.AB3 (GND), U1.AB24 (GND), U1.AD4 (GND), U1.AD7 (GND), U1.AD10 (GND), U1.AD13 (GND), U1.AD16 (GND), U1.AD19 (GND), U1.AD22 (GND), U1.AE1 (GND), U1.AE25 (GND), U1.B4 (GND), U1.C1 (GND), U1.C4 (GND), U1.C6 (GND), U1.C10 (GND), U1.D3 (GND), U1.D6 (GND), U1.D8 (GND), U1.E5 (GND), U1.E6 (GND), U1.E7 (GND), U1.F5 (GND), U1.F6 (GND), U1.F7 (GND), U1.F8 (GND), U1.G3 (GND), U1.G10 (GND), U1.G19 (GND), U1.H6 (JTAG_MOD), U1.H8 (GND), U1.H12 (GND), U1.H15 (GND), U1.H18 (GND), U1.J2 (GND), U1.J8 (GND), U1.J12 (GND), U1.J15 (GND), U1.J18 (GND), U1.K8 (GND), U1.K10 (GND), U1.K12 (GND), U1.K15 (GND), U1.K18 (GND), U1.L2 (GND), U1.L5 (GND), U1.L8 (GND), U1.L10 (GND), U1.L12 (GND), U1.L15 (GND), U1.L18 (GND), U1.M8 (GND), U1.M10 (GND), U1.M12 (GND), U1.M15 (GND), U1.M18 (GND), U1.N8 (GND), U1.N10 (GND), U1.N15 (GND), U1.N18 (GND), U1.P8 (GND), U1.P10 (GND), U1.P12 (GND), U1.P15 (GND), U1.P18 (GND), U1.R8 (GND), U1.R12 (GND), U1.R15 (GND), U1.R17 (GND), U1.T8 (GND), U1.T11 (GND), U1.T12 (GND), U1.T15 (GND), U1.T17 (GND), U1.T19 (GND), U1.U8 (GND), U1.U11 (GND), U1.U12 (GND), U1.U15 (GND), U1.U17 (GND), U1.U19 (GND), U1.V8 (GND), U1.V19 (GND)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; also elsewhere on the board
HDMI_VP: C78.1, U1.N12 (VDD_CACHE_CAP), U1.R10 (VDD_SOC_CAP), U1.T10 (VDD_SOC_CAP), U1.T13 (VDD_SOC_CAP), U1.T14 (VDD_SOC_CAP), U1.U10 (VDD_SOC_CAP), U1.U13 (VDD_SOC_CAP), U1.U14 (VDD_SOC_CAP); also elsewhere on the board
HDMI_VPH: JP6.1 (A), R38.1, U1.H10 (VDD_HIGH_CAP), U1.J10 (VDD_HIGH_CAP); also elsewhere on the board
I2C1_SCL: IC3.54 (SCL), R6.2; also elsewhere on the board
I2C1_SDA: IC3.53 (SDA), R37.2; also elsewhere on the board
MLB_SN: U1.A9 (MLB_SN); also elsewhere on the board
NVCC_PLL_OUT: C83.1, U1.E8 (NVCC_PLL_OUT)
unnamed: BT1.1 (+), IC3.42 (LICELL)
unnamed: C81.1, R38.2
unnamed: C108.2, R18.2
unnamed: IC3.8 (SW1ALX), IC3.9 (SW1BLX), L2.2
unnamed: IC3.11 (SW1CLX), L3.2
unnamed: IC3.22 (SW2LX), L5.2
unnamed: IC3.35 (SW3BLX), IC3.36 (SW3ALX), L6.1
unnamed: C89.1, IC3.49 (VCORE)
unnamed: C88.1, IC3.51 (VCOREDIG), R30.1
unnamed: C87.1, IC3.52 (VCOREREF)
unnamed: IC3.47 (VDDOTP), JP1.2 (B), JP3.1 (A), TP2.1
unnamed: C14.2, C15.1, IC3.29 (VHALF)
unnamed: J1.A5 (CC1), R21.2
unnamed: J1.B5 (CC2), R22.2
unnamed: J2.A5 (CC1), R23.1
unnamed: J2.B5 (CC2), R24.1
unnamed: C109.2, C110.2, J12.1, JP2.2 (B), L7.2, R19.2
unnamed: C73.1, JP1.1 (A)
unnamed: JP3.2 (B), R30.2
unnamed: R18.1, RT1.1 (COMP)
unnamed: R19.1, R20.2, RT1.7 (FB)
unnamed: L7.1, RT1.5 (LX)
unnamed: R16.2, RT1.8 (PGOOD)
unnamed: R17.2, RT1.6 (RT)
unnamed: C107.2, RT1.2 (SS)
unnamed: J2.A7 (D-), J2.B7 (D-), U1.F10 (USB_H1_DN)
unnamed: J2.A6 (D+), J2.B6 (D+), U1.E10 (USB_H1_DP)
unnamed: J1.A7 (D-), J1.B7 (D-), U1.B6 (USB_OTG_DN)
unnamed: J1.A6 (D+), J1.B6 (D+), U1.A6 (USB_OTG_DP)
ONOFF: SW1.1, U1.D12 (ONOFF)
PMIC_ON_REQ: C104.1, IC3.56 (PWRON), R15.1, SW2.2, U1.D11 (PMIC_ON_REQ)
PMIC_STBY_REQ: IC3.4 (STANDBY), U1.F11 (PMIC_STBY_REQ)
PMIC_VIN: C45.2, C46.2, C47.2, C48.2, C49.2, C50.2, C51.2, C52.2, C54.2, C55.1, C57.1, C58.1, C59.1, C65.2, C71.1, C72.1, C119.2, IC3.7 (SW1AIN), IC3.10 (SW1BIN), IC3.12 (SW1CIN), IC3.20 (SW4IN), IC3.23 (SW2IN_1), IC3.24 (SW2IN_2), IC3.27 (VIN2), IC3.34 (SW3BIN), IC3.37 (SW3AIN), IC3.45 (SWBSTIN), IC3.50 (VIN), IC3.55 (VDDIO), J12.2, JP2.1 (A), R6.1, R37.1; also elsewhere on the board
POR_B: IC3.3 (RESETBMCU), U1.C11 (POR_B); also elsewhere on the board
SNVS_PWR: IC3.43 (VSNVS), J10.2, J11.2, R13.1, R14.1, R15.2, U1.G11 (VDD_SNVS_IN)
VDD_ARM23_CAP: C77.1, U1.H11 (VDD_ARM23_CAP), U1.J11 (VDD_ARM23_CAP), U1.K11 (VDD_ARM23_CAP), U1.L11 (VDD_ARM23_CAP), U1.M11 (VDD_ARM23_CAP), U1.N11 (VDD_ARM23_CAP), U1.P11 (VDD_ARM23_CAP), U1.R11 (VDD_ARM23_CAP)
VDD_ARM_CAP: C76.1, U1.H13 (VDD_ARM_CAP), U1.J13 (VDD_ARM_CAP), U1.K13 (VDD_ARM_CAP), U1.L13 (VDD_ARM_CAP), U1.M13 (VDD_ARM_CAP), U1.N13 (VDD_ARM_CAP), U1.P13 (VDD_ARM_CAP), U1.R13 (VDD_ARM_CAP)
VDD_PU_CAP: C79.1, C80.1, U1.H17 (VDD_PU_CAP), U1.J17 (VDD_PU_CAP), U1.K17 (VDD_PU_CAP), U1.L17 (VDD_PU_CAP), U1.M17 (VDD_PU_CAP), U1.N17 (VDD_PU_CAP), U1.P17 (VDD_PU_CAP)
VDD_SNVS_CAP: C84.1, U1.G9 (VDD_SNVS_CAP)
VDD_USB_CAP: C82.1, U1.F9 (VDD_USB_CAP)
VGEN3_PWR: C64.1, IC3.26 (VGEN3), JP5.1 (A)

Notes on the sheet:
5.1k pulled down = 1.5A @ 5V max = 7.5W
< 4.8v
3.0V/3.3V
1.8V
1.0V
RTL8723BS
To PCIE
2.5V
3.0V
5.0V
min 85mOhm ESR as per checklist and EB814.pdf
< 3.6v
< 3.4v
1.2V
1.5V
PIN USAGE: 1- RT8070 output 2- Powers PMIC directly 2.8V-4.2V 3- GND
SDHC
3.3V
eMMC
1.375V
2.8V
NAND/DDR
USB SOC has: 1 USB OTG - We will use this as 'peripheral' and source power from it 3 USB hosts - 1 with usb PHY - 2 with HSIC CC pins: USB_OTG_CHD_B: NC Senses charger detect and tells PMIC if batter should be charged. We might do a standard ADC for CC voltage check only for logging, not for high p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
Unused switching regulators should be connected as follow: Pins SWxLX and SWxFB should be unconnected and Pin SWxIN should be connected to VIN with a 0.1 μF bypass capacitor.
INTERNAL LDOS VDD_HIGH_CAP = 204mA - SATA_VPH = 13 + 7 = 20mA - PCIE_VPH = 20mA - HDMI_VPH = 14mA - MIPI = ?? - LVDS = ?? - GETH_2V5 = 150mA VDD_SOC_CAP = 69.1mA - SATA_VP = 18mA - PCIE_VP = 47mA - HDMI_VP = 4.1mA
PWR SEQ and assignment MMPF0100F0ANES (F0 OTP mode) 1- VDD_SNVS_IN powered first (3.0V) 2- POR_B asserted low until VDD_ARM_CAP VDD_SOC_CAP VDD_PU_CAP stable 3- VDD_ARM_IN(996MHz max) and VDD_SOC_IN any order (1.375) ================================== 5V from USB OTG RT8070 outputs 3.3V from this a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
UNPOWERED VREF_DDR Any VGEN
POWER REQUIREMENTS ================== Max gaming power needed: VDD_ARM = 1625mA (2069 mW) VDD_SOC = 1250 (1555mW) VDD_HIGH = 54mA85 (126 mW) VDD_DDR +chip = 1390 (1995 mW) Total = 6W max! eMMC max = 100mA @ 3.3 NAND max = 35mA @ 3.3 (116 mW) LCD logic = 3.3v 220mA VSC8531XMW-02 SATA / PCIE ? Wifi/R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
BOOT MODE[1:0] b'00 = BT_FUSE_SEL ? Gpio boot (defaults SD) : serial download b'01 = Serial Downloader (USB OTG1 for 90 sec) b'10 = Internal boot eMMC: SD3 8pin Also can boot: SD1/uSDHC 4pin
Main XTAL ECS-240-8-36CKM-TR xx 24MHz 8pF load capacitance 100uW drive ESR:60mOHM Caps: 6pF - 12pF XRCGB24M000FBP12R0 <== 24MHz 6pF 2.0 x 1.6mm 300uW max ESR: 80Ohm RTC: ECS-.327-12.5-34B-TR 12.5pF load capacitance Caps: 15pF - 21pF
CLOCKS Copying SABRE board CLK1 drives PCIe CLK2 is NC MediaLB pins unused
